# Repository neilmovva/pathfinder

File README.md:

pathfinder - wearable navigation for the blind
==========

Current Status:
HW Board Family - Tacitus G3 / PG-3XX
(note: HW builds go by the internal codename "Tacitus")

[See here](http://neilmovva.github.io/pathfinder/) for an overview of what we're doing, and why. [Engineering updates are here](https://hackaday.io/project/2372-pathfinder-haptic-navigation#menu-logs) for now - we're working on getting a more cohesive project site together.

Pathfinder is a glove that translates distance into haptic feedback. Users just wear the glove and point at objects up to 500 centimeters away, and feel gentle pulses corresponding to the object's distance. It’s designed to give the user greater freedom of motion and longer operational range when compared to traditional navigation solutions for the blind, such as the cane. I incorporated research ranging from embedded electronics to the neuroscience of touch to turn this simple concept into the best prototype I could, before sharing the device with my local community center for the blind.

I'm currently working through iterative prototypes, so the repository may be a little unorganized at times. Please raise any specific questions in the issue tracker.

LICENSE: CC BY-NC-SA

All work in this repository is licensed under CC BY-NC-SA, "which lets others remix, tweak, and build upon your work non-commercially, as long as they credit you and license their new creations under identical terms."

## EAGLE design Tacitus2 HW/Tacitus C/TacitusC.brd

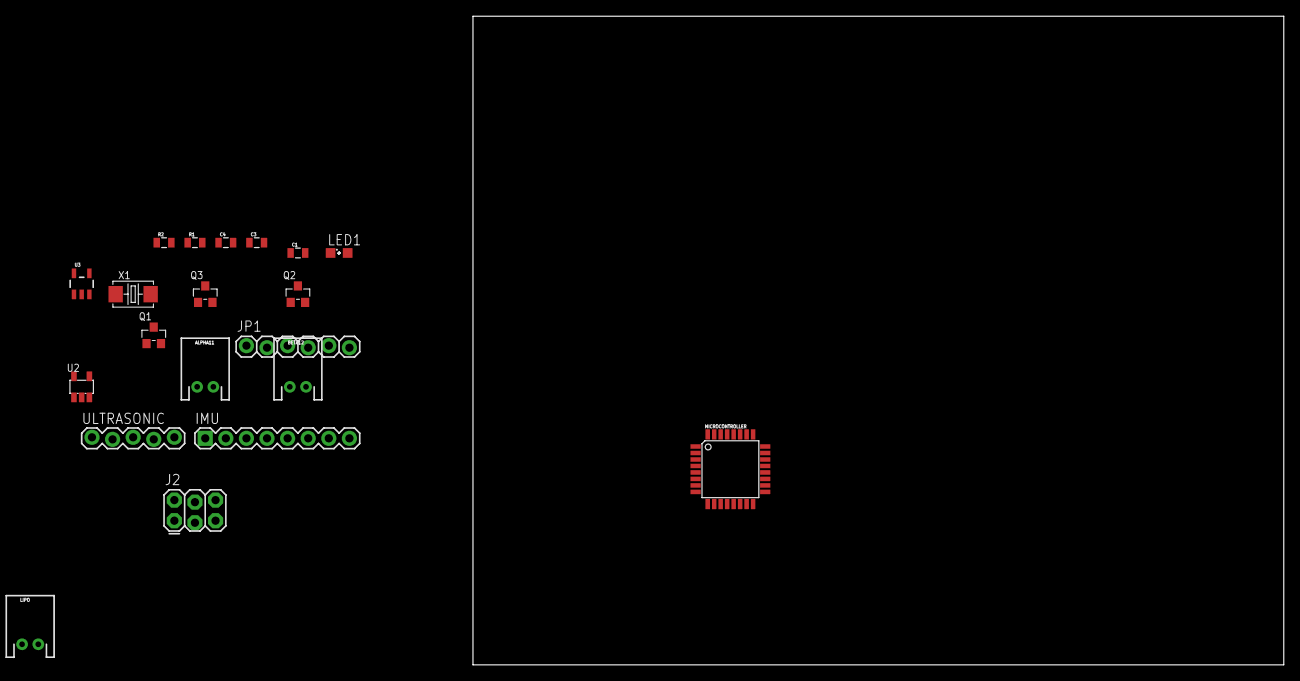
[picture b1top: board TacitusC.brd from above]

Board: 2 copper layers, 100.0 x 80.0 mm, 20 parts (0 on the bottom side), 19 nets, no tracks yet.

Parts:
ALPHA11: M02JST-PTH-2; JST-2-PTH
BETA12: M02JST-PTH-2; JST-2-PTH
C1: 10uF; 0805
C3, C4: 22pF; 0805
IMU: MPU-6050; 1X08
J2: AVR_SPI_PRG_62X3_LOCK; 2X3_LOCK
JP1: 1X06_LOCK
LED1: SML0805
LIPO: M02JST-PTH-2; JST-2-PTH
MICROCONTROLLER: ATMEGA328; TQFP32-08
Q1, Q2: MOSFET-N-044020001; SOT23
Q3: MOSFET-P-044021001; SOT23
R1, R2: 10K; 0805
U2: MIC5205-3.3YM5-1300180P1; SOT23-5
U3: MCP73831; SOT23-5
ULTRASONIC: US-100; 1X05_LOCK
X1: 16MHz-CRYSTAL; 2P-SMD-5.0X3.2

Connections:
GND: C1.1, C3.1, C4.1, IMU.2, J2.6, JP1.5, JP1.6, LED1.C, LIPO.1, MICROCONTROLLER.3, MICROCONTROLLER.5, MICROCONTROLLER.21, Q1.2, Q2.2, R1.1, R2.1, U2.2, U3.2, ULTRASONIC.1, ULTRASONIC.2
MC_RX: JP1.3, MICROCONTROLLER.30
MC_TX: JP1.2, MICROCONTROLLER.31
unnamed: C1.2, J2.2, JP1.4, MICROCONTROLLER.4, MICROCONTROLLER.6, MICROCONTROLLER.18, Q3.1, R1.2, U2.5, U3.4
unnamed: C4.2, MICROCONTROLLER.8
unnamed: C3.2, MICROCONTROLLER.7
unnamed: MICROCONTROLLER.15, Q1.1
unnamed: LIPO.2, Q3.2, U3.3
unnamed: MICROCONTROLLER.12, ULTRASONIC.4
unnamed: R2.2, U3.5
unnamed: LED1.A, U3.1
unnamed: MICROCONTROLLER.16, Q2.1
unnamed: ALPHA11.2, Q1.3
unnamed: BETA12.2, Q2.3
unnamed: IMU.3, MICROCONTROLLER.28
unnamed: IMU.4, MICROCONTROLLER.27
unnamed: MICROCONTROLLER.13, ULTRASONIC.3
RST: J2.5, JP1.1, MICROCONTROLLER.29
V_BATT: ALPHA11.1, BETA12.1, IMU.1, Q3.3, U2.1, U2.3, ULTRASONIC.5

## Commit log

2014-04-05 Re-up of existing resources.
2014-04-05 More cleanup!
2014-04-05 Done with ds_store!
2014-04-05 cleanup
2014-04-07 Rollback to ATmega328, using NewSoftSerial instead of hardware UART
2014-04-08 Custom HW designs in!
2014-04-09 early schematic release
2014-04-10 keepup
2014-04-30 improved design for fabrication/assembly tolerances
2014-07-05 Began new design in Proteus, stepping D
2014-07-05 Added writing repo, cleaned old testing boards
2014-07-24 push of TacD HW files
2014-08-26 abstract added
2014-10-27 stripped LR functions, added hybrid b/w teensy 3.1 and atmega328p
2015-06-15 Total overhaul of the workbase. However, this organization reflects my own personal workspace, and may be a little dificult to navigate as I clean things up.
2015-06-15 More cleanup to improve directory structure.
2015-06-15 More restructuring to clear some build issues
2015-06-18 Reduced FIFO output rate to 100 Hz. Added calibration routines (not yet active)
2015-06-18 Reduced sonar echo wait time to speed up distance collection. Marginally reduced haptic pulse duration.
2015-06-18 Added print debugging handles to speed up "production" builds
2015-06-18 Fixed faceDown angle detection (negative pitch is "down"). Reorganization of debug handles and constants.
2015-06-18 Temporarily disabled sensor calibration. Rolled modified library files into new source directory. Unmodified lib files not included; Pathfinder still requires the I2CDev, MPU-6050, and Arduino standa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
2015-06-18 Performed chip specific calibration on all 6-axes (G2-200)
2015-06-18 Increased DMP read rate to 200 Hz, in effort to reduce spatial lag.
2015-06-19 Slowed IMU data to provide simple hysteresis for faceDown detection. Added LED indication for system states (e.g. faceDown, more to come). Minor optimizations.
2015-06-28 started writing EEPROM set-and-forget calibration features
2015-07-09 Preliminary support for PG-3XX board family. Minor optimzations. TODO: Need automated IMU calibration.
2015-07-13 Added calibration functionality and storage of device-specific values. EEPROM function may be exhibiting data overflow, further testing required.
2015-07-13 Next generation HW, will be forked to new family (H-series). Planned changes: Fix onboard LiPo charging USB-SER converter on board (CH340G) Switch to smaller ICSP (tag-connect) TQFP -> QFN MCU Denser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
2015-07-14 large repo reorganization
2015-07-14 more reorg
2015-07-18 Moved all SW related files into a new subfolder. All dependencies are now bundled with the project, so Pathfinder can be built in any Arduino environment. I wanted to include all sources in their own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
2016-02-17 Create gh-pages branch via GitHub
2017-01-19 adding headline image

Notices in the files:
parts and their libraries:
SparkFun-DigitalIC: Licensing: Creative Commons ShareAlike 4.0 International - https://creativecommons.org/licenses/by-sa/4.0
